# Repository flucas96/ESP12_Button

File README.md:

# ESP12_Button
:)

--> button - AA = Button mit einer AA-Batterie (ohne Timer)

--> button - AAA = Button mit einere AAA-Batterie (ohne Timer)

__________________________________________________________________________________________________________________________________

--> V.1.2.1 Coin Cell & V.1.2.2 Coin Cell sind gleich groß. (Unabhängig auch vom Timer der benutzt wird)

--> V.1.2.1 LIPO & V.1.2.2 LIPO sind gleich groß. (Unabhängig auch vom Timer der benutzt wird)

__________________________________________________________________________________________________________________________________

--> V1.2 Coin Cell&Lipo & V1.2 Coin Cell&Lipo[TPL5110] & V1.2 Coin Cell&Lipo[NO Timer] sind gleich groß wie das V1.2_Mosfet[Experiment]

__________________________________________________________________________________________________________________________________

Problem: Der Boost Converter, welcher für die Coin Cell benötigt wird, schaltet durch wenn EN LOW ist anstatt den Stromfluss zu trennen. 
(Besteht nur bei den Versionen mit dem TPL5111) (Die Versionen deren Ordern mit "OLD" endet sind wahrscheinlich nicht voll funktionsfähig. 
Der ESP12 weiterhin Strom bekommen auch wenn der Timer LOW ist. Dadurch geht der Vorteil, der durch den Timer erreicht werden soll verloren 
und die Versionen sollten gleich gut performen (wenn nicht sogar schlechter) als die ohne Timer. Da, der Boost Converter für dieses Verhalten
verantworlich ist, tretten die Probleme nur bei den Versionen, welche die Nutzung einer Coin Cell voraussehen, auf.

Lösungen: Anderer Boost Converter ()/ Transistor der den ESP zusätzlich an/ausschaltet (V1.2.3) / TPL5110 verwenden (v1.2 / v1.2.3)

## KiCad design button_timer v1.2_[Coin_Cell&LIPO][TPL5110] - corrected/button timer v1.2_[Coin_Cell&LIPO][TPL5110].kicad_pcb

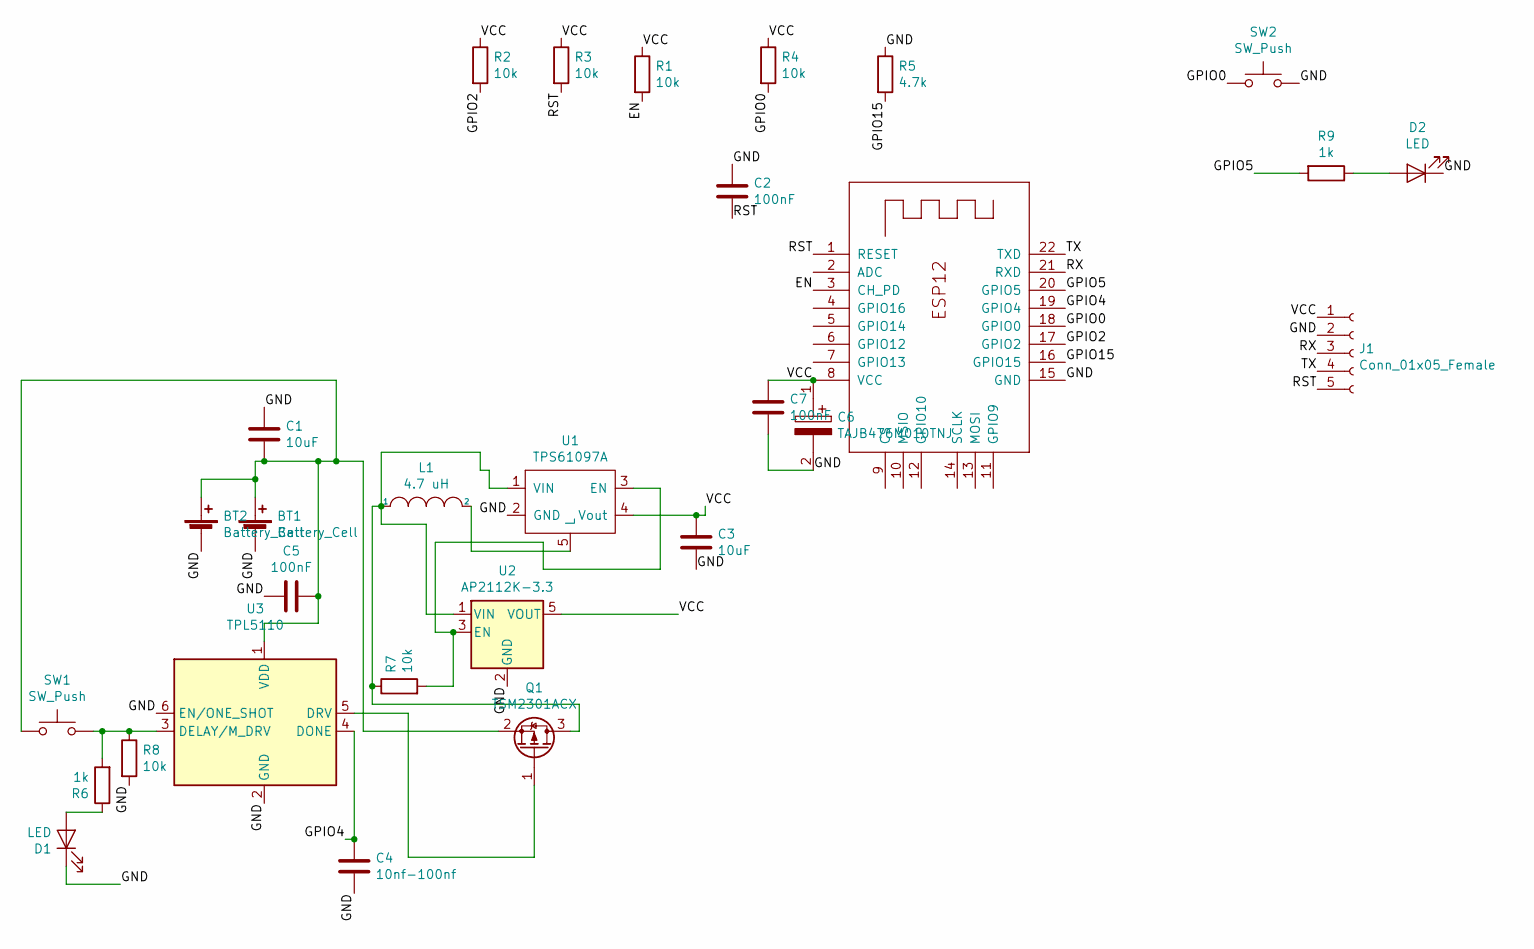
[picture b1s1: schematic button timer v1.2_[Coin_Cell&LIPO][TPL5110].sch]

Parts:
BT1: Battery_Cell; BatteryHolder_Keystone_1058_1x2032
BT2: Battery_Cell; JST_PH_B2B-PH-K_1x02_P2.00mm_Vertical
C1, C3: 10uF; C_0805_2012handsodermod
C2, C5: 100nF; C_0805_2012handsodermod
C4: 10nf-100nf; C_0402_1005Metric_Pad0.74x0.62mm_HandSolder
C6: TAJB476M010TNJ; CAPPM3528X210N; Manufacturer_Part_Number TAJB476M010TNJ; Mouser Part Number 581-TAJB476M010TNJ
C7: 100nF; C_0402_1005Metric_Pad0.74x0.62mm_HandSoldermod
D1: LED; LED_1206_3216Metric_Castellated
D2: LED; LED_0805_2012Metric_Castellated_mod
J1: Conn_01x05_Female; PinSocket_1x05_P2.54mm_Vertical_mod
L1: 4.7 uH; SMD-1210_Pol_inductor
Q1: TSM2301ACX; SOT-23
R1, R2, R3, R4, R7, R8: 10k; R_0805_2012handsoldermod
R5: 4.7k; R_0805_2012handsoldermod
R6, R9: 1k; R_0805_2012handsoldermod
SW1: SW_Push; SW_PUSH_6mm_H8mm_mod
SW2: SW_Push; SW_SPST_B3U-1000P_mod
U1: TPS61097A; SOT-23-5_HandSolderingmod
U2: AP2112K-3.3; SOT-23-5_HandSolderingmod
U3: TPL5110; SOT-23-6handsoldering
X1: ESP-12E; ESP-12Elesssilk

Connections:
/EN: R1.2, X1.3 (CH_PD)
/GND: BT1.2 (-), BT2.2 (-), C1.1, C2.1, C3.2, C4.2, C5.2, C6.2, C7.2, D1.1 (K), D2.1 (K), J1.2, R5.1, R8.2, SW2.2, U1.2 (GND), U2.2 (GND), U3.2 (GND), U3.6 (EN/ONE_SHOT), X1.15 (GND)
/GPIO0: R4.2, SW2.1, X1.18 (GPIO0)
/GPIO2: R2.2, X1.17 (GPIO2)
/GPIO4: C4.1, U3.4 (DONE), X1.19 (GPIO4)
/GPIO5: R9.2, X1.20 (GPIO5)
/GPIO15: R5.2, X1.16 (GPIO15)
/RST: C2.2, J1.5, R3.2, X1.1 (RESET)
/RX: J1.3, X1.21 (RXD)
/TX: J1.4, X1.22 (TXD)
/VCC: C3.1, C6.1, C7.1, J1.1, R1.1, R2.1, R3.1, R4.1, U1.4 (Vout), U2.5 (VOUT), X1.8 (VCC)
unnamed: BT1.1 (+), BT2.1 (+), C1.2, C5.1, Q1.2 (S), SW1.1, U3.1 (VDD)
unnamed: D1.2 (A), R6.1
unnamed: D2.2 (A), R9.1
unnamed: L1.1, Q1.3 (D), R7.1, U1.1 (VIN), U2.1 (VIN)
unnamed: L1.2, U1.5 (L)
unnamed: Q1.1 (G), U3.5 (DRV)
unnamed: R6.2, R8.1, SW1.2, U3.3 (DELAY/M_DRV)
unnamed: R7.2, U1.3 (EN), U2.3 (EN)

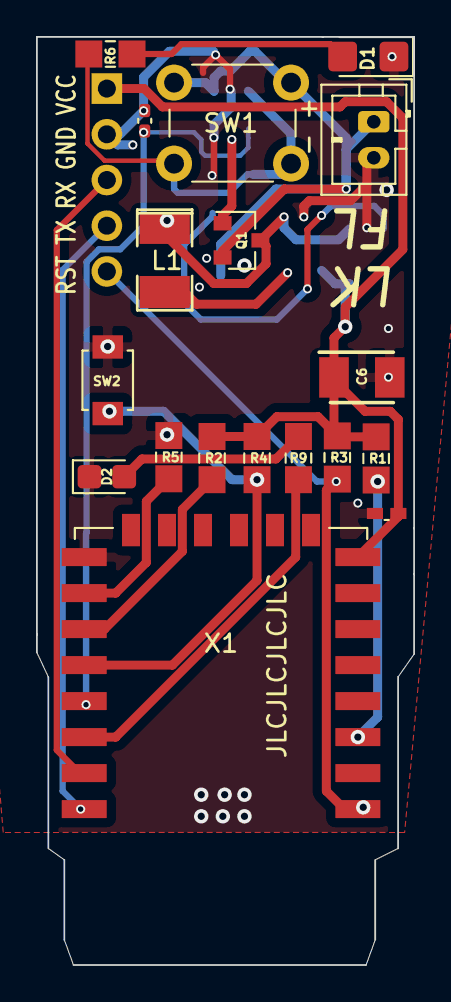
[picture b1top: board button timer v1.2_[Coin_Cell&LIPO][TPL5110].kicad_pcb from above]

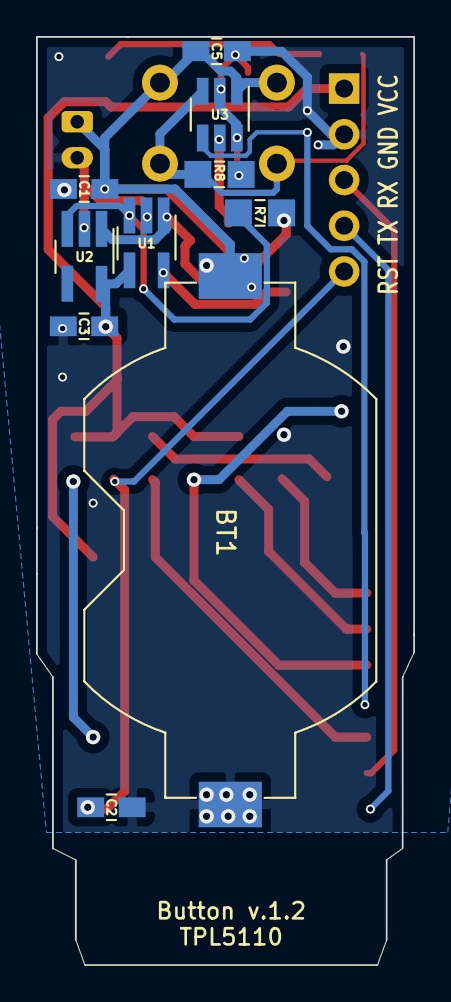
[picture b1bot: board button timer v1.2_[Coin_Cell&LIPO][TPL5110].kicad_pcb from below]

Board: 2 copper layers, 21.0 x 51.6 mm, 29 parts (10 on the bottom side), 19 nets.

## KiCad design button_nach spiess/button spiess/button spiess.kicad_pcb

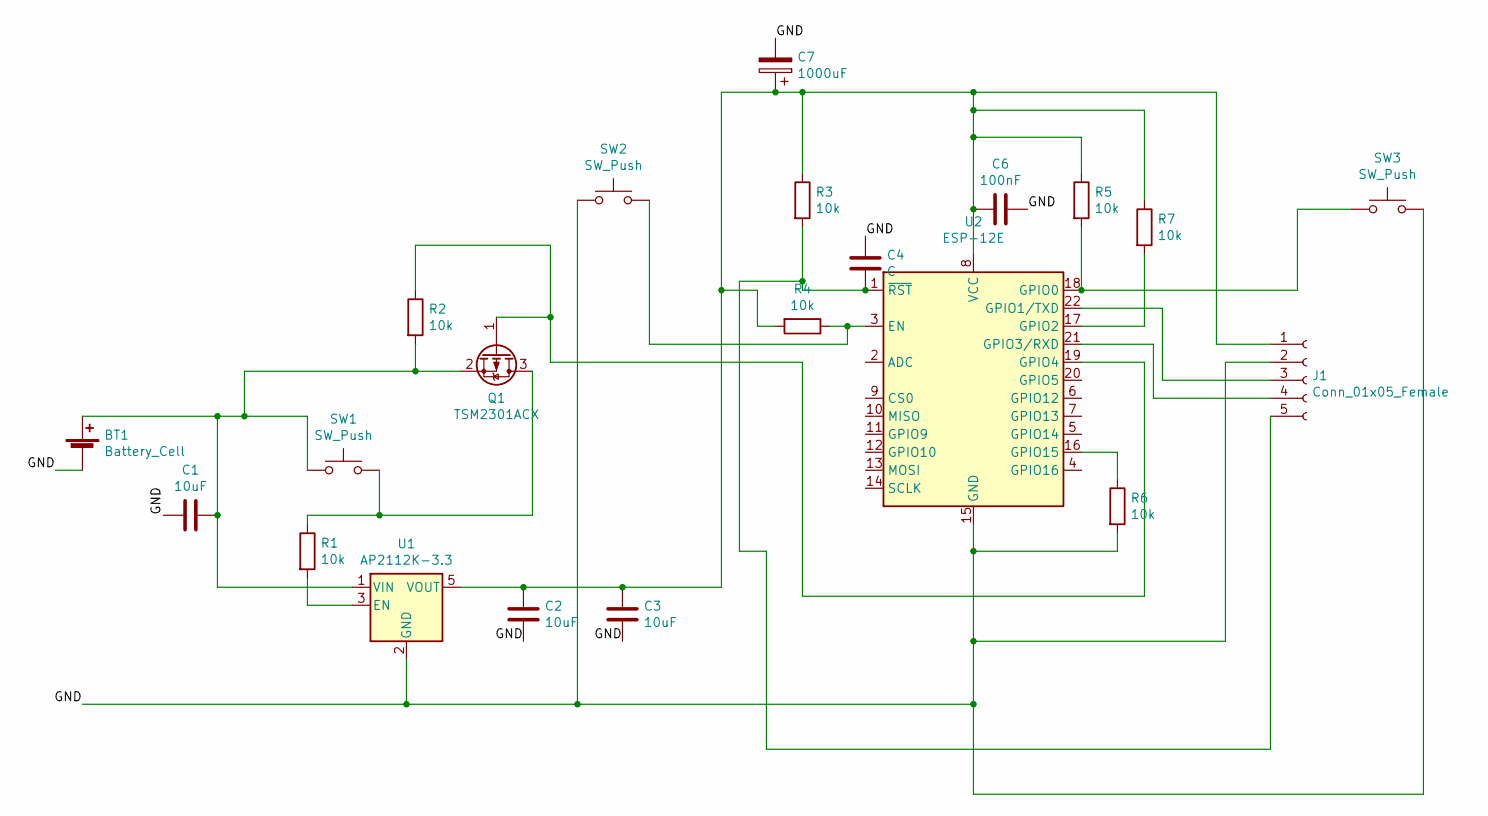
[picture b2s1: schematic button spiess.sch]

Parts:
BT1: Battery_Cell; BatteryHolder_Keystone_3008_1x2450
C1, C2, C3: 10uF; C_0805_2012handsodermodmod
C4: C; C_0402_1005Metric_Pad0.74x0.62mm_HandSoldermod
C6: 100nF; C_0402_1005Metric_Pad0.74x0.62mm_HandSoldermod
C7: 1000uF; CP_Elec_6.3x3
J1: Conn_01x05_Female; PinSocket_1x05_P2.54mm_Vertical_mod
Q1: TSM2301ACX; SOT-23
R1, R2, R3, R4, R5, R6, R7: 10k; R_0603_1608Metric_Pad0.98x0.95mm_HandSolder_mod
SW1: SW_Push; SW_PUSH_6mm_H8.5mm
SW2, SW3: SW_Push; SW_SPST_B3U-1000P
U1: AP2112K-3.3; SOT-23-5_HandSolderingmod
U2: ESP-12E; ESP-12Elesssilk

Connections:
/GND: BT1.2 (-), C1.2, C2.2, C3.2, C4.1, C6.1, C7.2, J1.2, R6.2, SW2.1, SW3.2, U1.2 (GND), U2.15 (GND)
unnamed: BT1.1 (+), C1.1, Q1.2 (S), R2.2, SW1.1, U1.1 (VIN)
unnamed: C2.1, C3.1, C6.2, C7.1, J1.1, R3.1, R4.2, R5.1, R7.1, U1.5 (VOUT), U2.8 (VCC)
unnamed: C4.2, J1.5, R3.2, U2.1 (~RST)
unnamed: J1.3, U2.22 (GPIO1/TXD)
unnamed: J1.4, U2.21 (GPIO3/RXD)
unnamed: Q1.1 (G), R2.1, U2.19 (GPIO4)
unnamed: Q1.3 (D), R1.1, SW1.2
unnamed: R1.2, U1.3 (EN)
unnamed: R4.1, SW2.2, U2.3 (EN)
unnamed: R5.2, SW3.1, U2.18 (GPIO0)
unnamed: R6.1, U2.16 (GPIO15)
unnamed: R7.2, U2.17 (GPIO2)

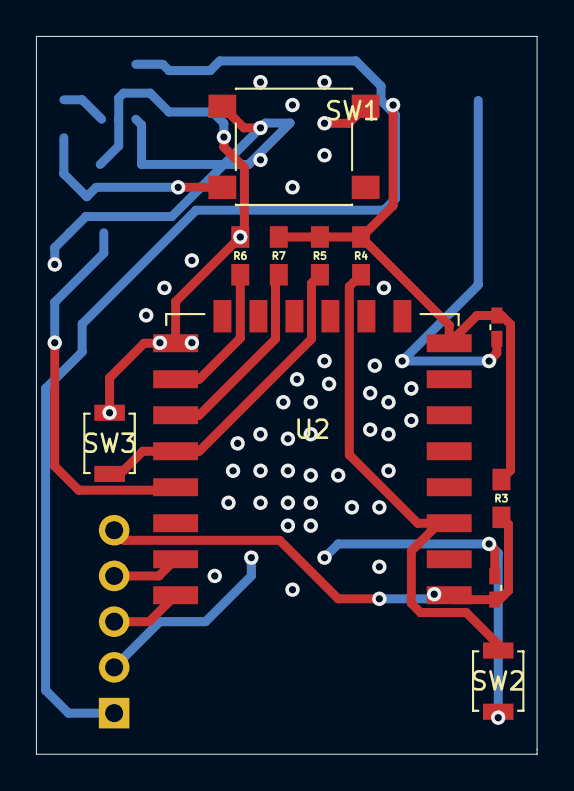
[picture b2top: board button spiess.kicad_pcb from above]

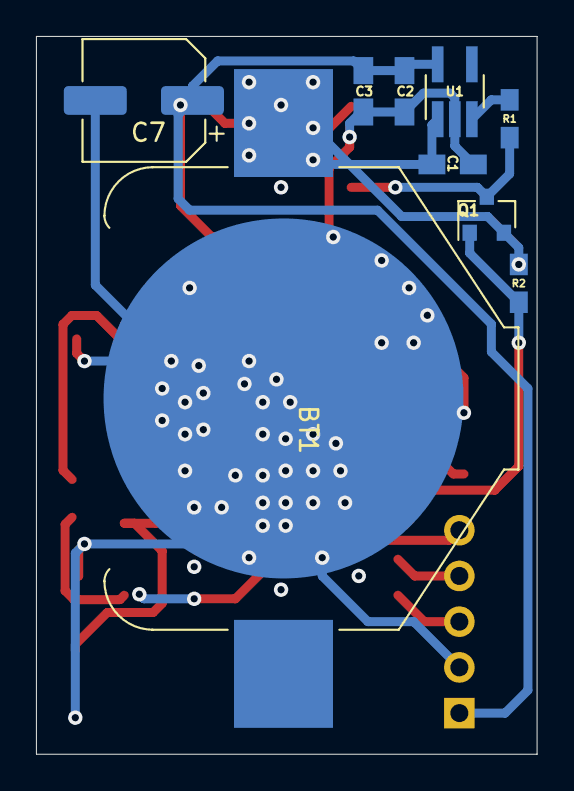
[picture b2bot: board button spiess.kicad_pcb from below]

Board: 2 copper layers, 27.8 x 39.9 mm, 21 parts (9 on the bottom side), 13 nets.

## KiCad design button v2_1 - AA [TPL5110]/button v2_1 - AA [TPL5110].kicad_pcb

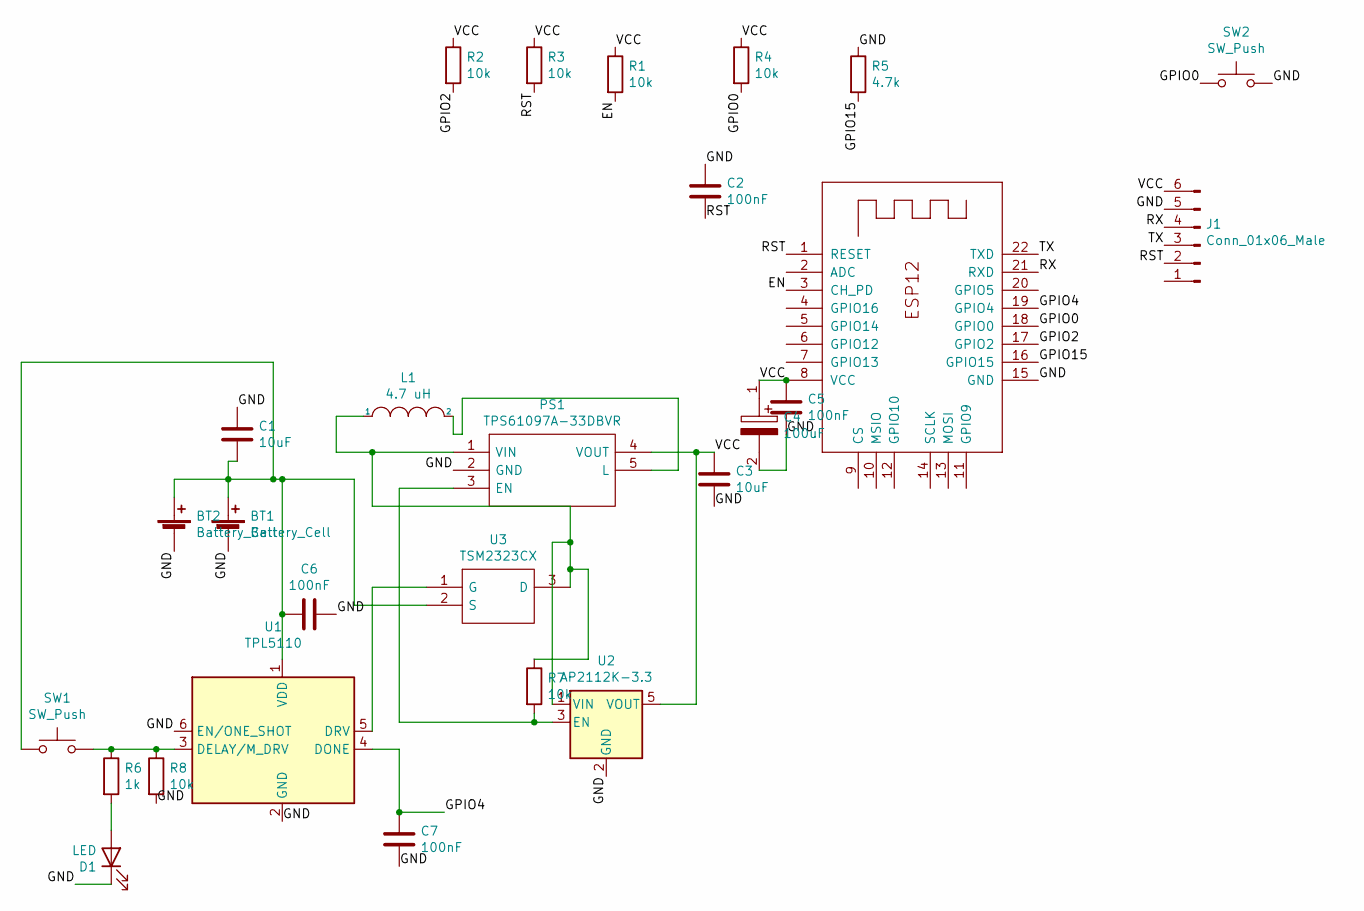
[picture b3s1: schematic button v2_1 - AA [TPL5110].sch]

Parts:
BT1: Battery_Cell; BatteryHolder_Keystone_2460_1xAA
BT2: Battery_Cell; JST_PH_B2B-PH-K_1x02_P2.00mm_Vertical
C1, C3: 10uF; C_0805_2012handsodermod
C2, C5, C6, C7: 100nF; C_0402_1005Metric_Pad0.74x0.62mm_HandSoldermod
C4: 100uF; CAPPM3528X210N; Manufacturer_Part_Number TAJB476M010TNJ; Mouser Part Number 581-TAJB476M010TNJ
D1: LED; LED_1206_3216Metric_Castellated
J1: Conn_01x06_Male; PinHeader_1x06_P2.54mm_Vertical
L1: 4.7 uH; SMD-1210_Pol_inductor
PS1: TPS61097A-33DBVR; SOT-23-5_HandSolderingmod; Manufacturer_Part_Number TPS61097A-33DBVR; Mouser Part Number 595-TPS61097A-33DBVR
R1, R2, R3, R4, R7: 10k; R_0805_2012handsoldermod
R5: 4.7k; R_0805_2012handsoldermod
R6: 1k; C_0805_2012handsodermodmod
R8: 10k; R_0603_1608Metric_Pad0.98x0.95mm_HandSolder_mod
SW1: SW_Push; SW_PUSH_6mm
SW2: SW_Push; button_smd_hmsensor
U1: TPL5110; SOT-23-6handsoldering
U2: AP2112K-3.3; SOT-23-5_HandSolderingmod
U3: TSM2323CX; SOT-23; Manufacturer_Part_Number TSM2323CX; Mouser Part Number 821-TSM2323CX
X1: ESP-12E; ESP-12Elesssilk

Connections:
/EN: R1.2, X1.3 (CH_PD)
/GND: BT1.2 (-), BT2.2 (-), C1.1, C2.1, C3.2, C4.2, C5.2, C6.1, C7.2, D1.1 (K), J1.5, PS1.2 (GND), R5.1, R8.2, SW2.2, U1.2 (GND), U1.6 (EN/ONE_SHOT), U2.2 (GND), X1.15 (GND)
/GPIO0: R4.2, SW2.1, X1.18 (GPIO0)
/GPIO2: R2.2, X1.17 (GPIO2)
/GPIO4: C7.1, U1.4 (DONE), X1.19 (GPIO4)
/GPIO15: R5.2, X1.16 (GPIO15)
/RST: C2.2, J1.2, R3.2, X1.1 (RESET)
/RX: J1.4, X1.21 (RXD)
/TX: J1.3, X1.22 (TXD)
/VCC: C3.1, C4.1, C5.1, J1.6, PS1.4 (VOUT), R1.1, R2.1, R3.1, R4.1, U2.5 (VOUT), X1.8 (VCC)
unnamed: BT1.1 (+), BT2.1 (+), C1.2, C6.2, SW1.1, U1.1 (VDD), U3.2 (S)
unnamed: D1.2 (A), R6.2
unnamed: L1.1, PS1.1 (VIN), R7.1, U2.1 (VIN), U3.3 (D)
unnamed: L1.2, PS1.5 (L)
unnamed: PS1.3 (EN), R7.2, U2.3 (EN)
unnamed: R6.1, R8.1, SW1.2, U1.3 (DELAY/M_DRV)
unnamed: U1.5 (DRV), U3.1 (G)

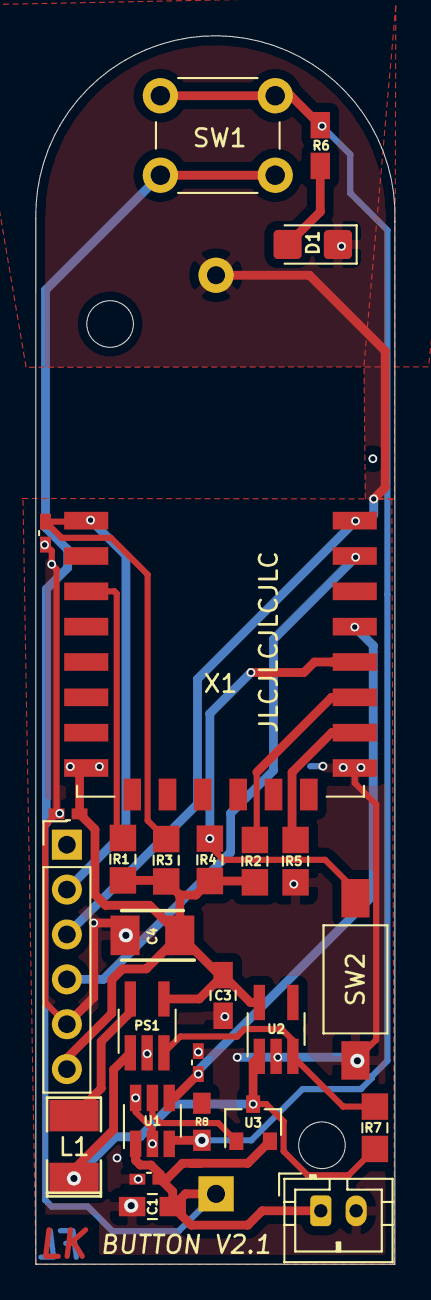
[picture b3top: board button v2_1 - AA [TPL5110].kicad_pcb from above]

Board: 2 copper layers, 20.3 x 69.5 mm, 27 parts (1 on the bottom side), 17 nets.

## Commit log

2021-02-22 clean up
2021-02-22 23.02 00:38
2021-02-22 23.02 00:40
2021-02-22 Update fp-info-cache
2021-02-23 23.02 13:31
2021-02-23 TPL 5110 version
2021-02-23 Bilder von den Maßen hinzugefügt
2021-02-23 :airplane:
2021-02-23 :rocket: :full_moon_with_face:
2021-02-23 3D Models etwas verbessert
2021-02-23 :rocket: :new_moon:
2021-02-23 TO THE MOON
2021-02-23 :rocket: :moon: :100:
2021-02-23 TO JUPITER :rocket:
2021-02-23 Silkscreen Update
2021-02-24 cap between esp vcc and ground added
2021-02-24 cap added between vcc and gnd of the esp
2021-02-24 Added 100nF decoupling capacitors between VCC and Ground of the ESP
2021-02-25 turned around some of the LIPO connectors
2021-02-26 added BOMs
2021-02-28 All Footprints corrected
2021-03-01 added timer version for AA and AAA
